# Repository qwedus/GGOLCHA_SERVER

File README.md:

# GGOOLCHA Telemetry System

DIY wireless data logging platform for Team GGOOLCHA

## Features

* 📡 Full wireless support
   * Real-time telemetry
   * Download recorded data 
   * Transmit User Events
   * Transmit CAN messages
   * Configure device (e.g. CAN bit rate)

* 📀 Up to 100 Hz data rate with various signals
   * 1x CAN 2.0(A/B)
   * 1x External GPS
   * 1x Internal 6-axis Accelerometer & Gyroscope
   * 4x Digital input channels
   * 6x Analog input channels
   * 1x Power supply voltage sensor
   * 1x Chip temperature sensor

* 💡 Customizable web-based data analysis tool
* 🍺 Fully Open-source & Open-hardware under the Beerware license

## Preview

[Web Control Hub](https://v2.monolith.luftaquila.io) for live telemetry, data viewer and device/ui configurations.

## Documentation

[Full documentation](https://v2.monolith.luftaquila.io/docs) for DIY and usage details.

## Others

The name of the project was inspired by Arthur C. Clark's novel `2001: A Space Odyssey`.

## Sponsors

The prototype PCBs for the Monolith v1, v2, and v2 mini were sponsored by [PCBWay](https://www.pcbway.com/).

For the detailed review of the manufactured PCB, see [here](https://v2.monolith.luftaquila.io/docs/#sponsor).

### Individuals

<!-- sponsors --><!-- sponsors -->

## 한계
현재는 stm32 -> esp32 -> mqtt 브로커 -> 서버 -> 프론트
stm32 -> esp32간 통신방식은 서버와 무관

JSON payload로 전달받을 경우
서버 JSON parser를 만들면 서버수정이 불필요할수도 있겠으나
 * JSON자체가 바이너리보다 무거움
 * JSON자체 오버헤드 존재등
 * WiFi자체 유선대비 지연/패킷손실 불규칙
 
 등등의 고빈도,고비용의 문제로 ESP32로는 바이너리 포맷이 적합하다고 판단.

따라서 현재로써는 Binary Payload방식을 이용할수밖에 없고 센싱을 금년과 다르게 할 경우 서버쪽 코드(protocol.js) 수정 불가피.

금년도에 사용한 ESP32의 경우 대역폭이 2.5GHZ로 낮았기때문에 호환성 최대화를 이용하여 아이폰 핫스팟이용(교내 와이파이 대역폭 5GHZ라 이용불가)

{2026년 3기 기준}

## Monolith v2 대비 변경사항
실시간 모니터링이 아닌 실시간 로깅을 목표로 했기때문에

브라우저가 MQTT브로커에 pub/sub클라이언트로 직접 접속하는 구조에 데이터 write가능한 상시 프로세스 추가구현(MQTT Logger)
시계열 DB인 influxDB 추가 구현및 운영.

다음 기수 이용을 고려하여 로컬보단 클라우드(AWS) 단일인스턴스내에 배포

deploy.yml 추가를 통해 CI/CD 구현. (GitHub 수정 즉시 서버 반영)  

센싱을 금년과 다르게 할 경우 (protocol.js)의 수정이 불가피하기에 수정의 편리함을 위해 기존에 하드 코딩되어있던 부분을 FIELD_SCHEMA 구조로 리팩토링
(필드의 추가/삭제의 경우 FIELD_SCHEMA만 변경하면 됨)

## 인프라 구축 과정

## LICENSE

For non-commercial use only:

```
"THE BEERWARE LICENSE" (Revision 42):
LUFT-AQUILA wrote this project. As long as you retain this notice,
you can do whatever you want with this stuff. If we meet someday,
and you think this stuff is worth it, you can buy me a beer in return.
```

<br>

<picture>
  <source media="(prefers-color-scheme: dark)" srcset="https://api.star-history.com/svg?repos=luftaquila/monolith&type=Date&theme=dark" />
  <source media="(prefers-color-scheme: light)" srcset="https://api.star-history.com/svg?repos=luftaquila/monolith&type=Date" />
  
</picture>

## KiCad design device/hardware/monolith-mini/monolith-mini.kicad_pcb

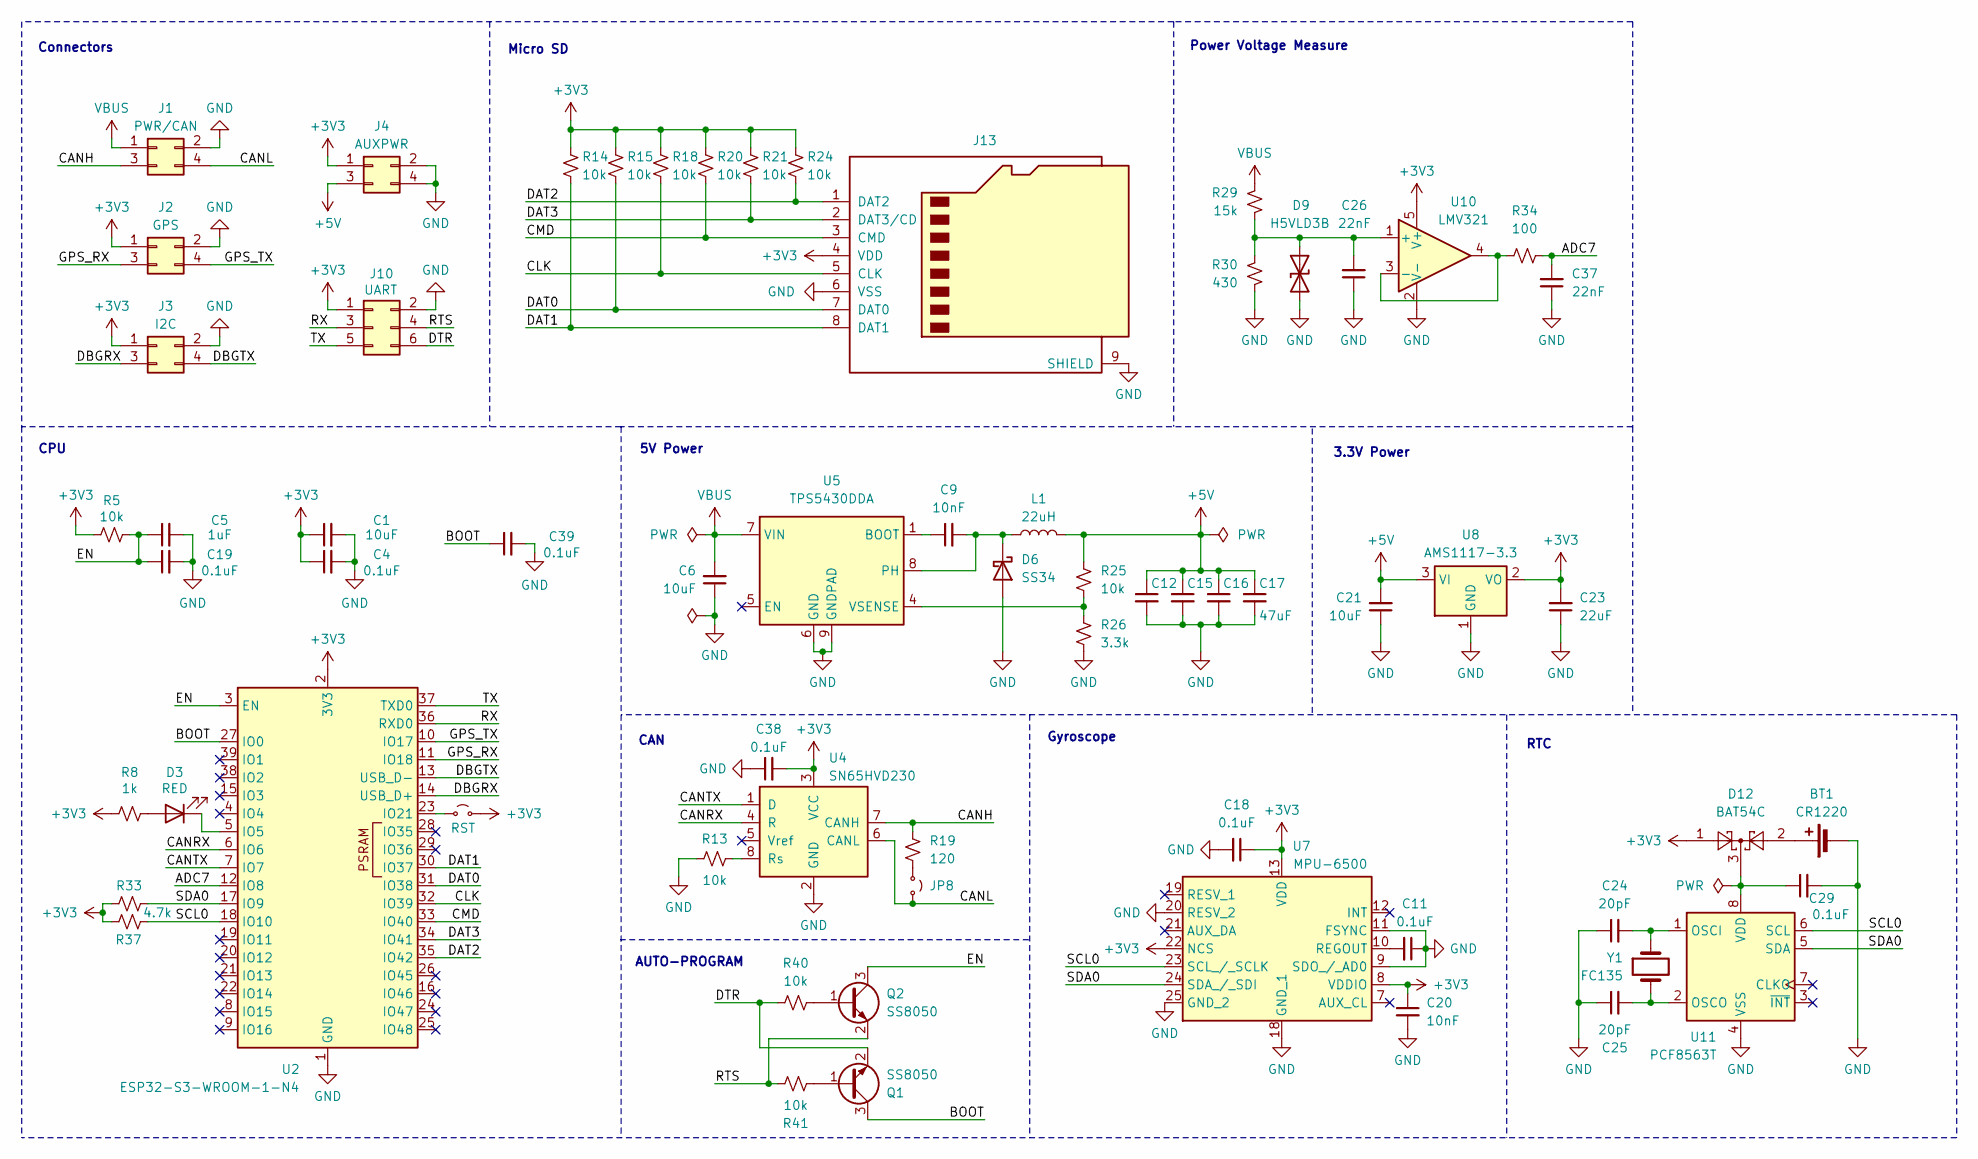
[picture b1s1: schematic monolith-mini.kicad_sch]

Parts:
BT1: CR1220; S8411-45R_1; Manufacturer_Part_Number CR1220-2; LCSC C70381
C1, C21: 10uF; C_0603_1608Metric; LCSC C19702
C4, C11, C18, C19, C29, C38, C39: 0.1uF; C_0603_1608Metric; LCSC C14663
C5: 1uF; C_0603_1608Metric; LCSC C15849
C6: 10uF; C_1206_3216Metric; LCSC C13585
C9, C20: 10nF; C_0603_1608Metric; LCSC C57112
C12, C15, C16, C17: 47uF; C_1206_3216Metric; LCSC C96123
C23: 22uF; C_0603_1608Metric; LCSC C59461
C24, C25: 20pF; C_0603_1608Metric; LCSC C1648
C26, C37: 22nF; C_0603_1608Metric; LCSC C21122
D3: RED; LED_0603_1608Metric; LCSC C2286
D6: SS34; D_SMA; LCSC C8678
D9: H5VLD3B; D_SOD-323; LCSC C20615805
D12: BAT54C; SOT-23; Manufacturer_Part_Number BAT54C; LCSC C37704
J1: PWR/CAN; Molex_Mini-Fit_Jr_5569-04A2_2x02_P4.20mm_Horizontal
J2: GPS; Molex_Mini-Fit_Jr_5569-04A2_2x02_P4.20mm_Horizontal
J3: I2C; Molex_Mini-Fit_Jr_5569-04A2_2x02_P4.20mm_Horizontal
J4: AUXPWR; Molex_Mini-Fit_Jr_5569-04A2_2x02_P4.20mm_Horizontal
J10: UART; PinHeader_2x03_P2.54mm_Vertical
J13: Micro_SD_Card; TF115BCP9; LCSC C393941
JP5: RST; PinHeader_1x02_P2.54mm_Vertical
JP8: CAN 120Ω; PinHeader_1x02_P2.54mm_Vertical
L1: 22uH; L_Sunlord_MWSA0603S; LCSC C177244
Q1, Q2: SS8050; SOT-23; LCSC C2150
R5, R13, R14, R15, R18, R20, R21, R24, R25, R40, R41: 10k; R_0603_1608Metric; LCSC C25804
R8: 1k; R_0603_1608Metric; LCSC C21190
R19: 120; R_0603_1608Metric; LCSC C22787
R26: 3.3k; R_0603_1608Metric; LCSC C22978
R29: 15k; R_0603_1608Metric; LCSC C22809
R30: 430; R_0603_1608Metric; LCSC C23170
R33, R37: 4.7k; R_0603_1608Metric; LCSC C23162
R34: 100; R_0603_1608Metric; LCSC C22775
U2: ESP32-S3-WROOM-1-N4; ESP32-S3-WROOM-1; LCSC C2913197
U4: SN65HVD230; SOIC-8_3.9x4.9mm_P1.27mm; LCSC C12084
U5: TPS5430DDA; TI_SO-PowerPAD-8_ThermalVias; LCSC C9864
U7: MPU-6500; QFN40P300X300X95-25N-D; Manufacturer_Part_Number MPU-6500; Mouser Part Number 410-MPU-6500
U8: AMS1117-3.3; SOT-223-3_TabPin2; LCSC C6186
U10: LMV321; SOT-23-5; LCSC C7972
U11: PCF8563T; SOIC-8_3.9x4.9mm_P1.27mm; LCSC C7440
Y1: FC135; Crystal_SMD_3215-2Pin_3.2x1.5mm; LCSC C32346

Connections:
+3V3: C1.1, C4.1, C18.1, C20.1, C23.2, C38.2, D12.1, J2.1, J3.1, J4.1, J10.1, J13.4 (VDD), JP5.2 (B), R5.2, R8.1, R14.2, R15.2, R18.2, R20.2, R21.2, R24.2, R33.1, R37.2, U2.2 (3V3), U4.3 (VCC), U7.8 (VDDIO), U7.13 (VDD), U7.22 (NCS), U8.2 (VO), U10.5 (V+)
+5V: C12.1, C15.1, C16.1, C17.1, C21.2, J4.3, L1.2, R25.2, U8.3 (VI)
/ADC7: C37.2, R34.2, U2.12 (IO8)
/BOOT: C39.1, Q1.3 (C), U2.27 (IO0)
/CANH: J1.3, R19.2, U4.7 (CANH)
/CANL: J1.4, JP8.2 (B), U4.6 (CANL)
/CANRX: U2.6 (IO6), U4.4 (R)
/CANTX: U2.7 (IO7), U4.1 (D)
/CLK: J13.5 (CLK), R18.1, U2.32 (IO39)
/CMD: J13.3 (CMD), R20.1, U2.33 (IO40)
/DAT0: J13.7 (DAT0), R15.1, U2.31 (IO38)
/DAT1: J13.8 (DAT1), R14.1, U2.30 (IO37)
/DAT2: J13.1 (DAT2), R24.1, U2.35 (IO42)
/DAT3: J13.2 (DAT3/CD), R21.1, U2.34 (IO41)
/DBGRX: J3.3, U2.14 (USB_D+)
/DBGTX: J3.4, U2.13 (USB_D-)
/DTR: J10.6, Q1.2 (E), R40.1
/EN: C5.1, C19.1, Q2.3 (C), R5.1, U2.3 (EN)
/GPS_RX: J2.3, U2.11 (IO18)
/GPS_TX: J2.4, U2.10 (IO17)
/RTS: J10.4, Q2.2 (E), R41.2
/RX: J10.3, U2.36 (RXD0)
/SCL0: R37.1, U2.18 (IO10), U7.23 (SCL_/_SCLK), U11.6 (SCL)
/SDA0: R33.2, U2.17 (IO9), U7.24 (SDA_/_SDI), U11.5 (SDA)
/TX: J10.5, U2.37 (TXD0)
GND: BT1.2 (-), C1.2, C4.2, C5.2, C6.1, C11.1, C12.2, C15.2, C16.2, C17.2, C18.2, C19.2, C20.2, C21.1, C23.1, C24.1, C25.1, C26.1, C29.2, C37.1, C38.1, C39.2, D6.2 (A), D9.2 (A2), J1.2, J2.2, J3.2, J4.2, J4.4, J10.2, J13.6 (VSS), J13.9 (SHIELD), R13.1, R26.1, R30.1, U2.1 (GND), U2.40 (GND), U2.41 (GND), U4.2 (GND), U5.6 (GND), U5.9 (GNDPAD), U7.9 (SDO_/_AD0), U7.11 (FSYNC), U7.18 (GND_1), U7.20 (RESV_2), U7.25 (GND_2), U8.1 (GND), U10.2 (V-), U11.4 (VSS)
unnamed: BT1.1 (+), D12.2
unnamed: D3.2 (A), R8.2
unnamed: D3.1 (K), U2.5 (IO5)
unnamed: C9.2, D6.1 (K), L1.1, U5.8 (PH)
unnamed: C26.2, D9.1 (A1), R29.1, R30.2, U10.1 (+)
unnamed: JP5.1 (A), U2.23 (IO21)
unnamed: JP8.1 (A), R19.1
unnamed: Q1.1 (B), R41.1
unnamed: Q2.1 (B), R40.2
unnamed: R13.2, U4.8 (Rs)
unnamed: C9.1, U5.1 (BOOT)
unnamed: R25.1, R26.2, U5.4 (VSENSE)
unnamed: C11.2, U7.10 (REGOUT)
unnamed: R34.1, U10.3 (-), U10.4
unnamed: C24.2, U11.1 (OSCI), Y1.1
unnamed: C25.2, U11.2 (OSCO), Y1.2
unnamed: C29.1, D12.3, U11.8 (VDD)
VBUS: C6.2, J1.1, R29.2, U5.7 (VIN)

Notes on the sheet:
CAN
AUTO-PROGRAM
Micro SD
Connectors
3.3V Power
RTC
Power Voltage Measure
CPU
Gyroscope
5V Power

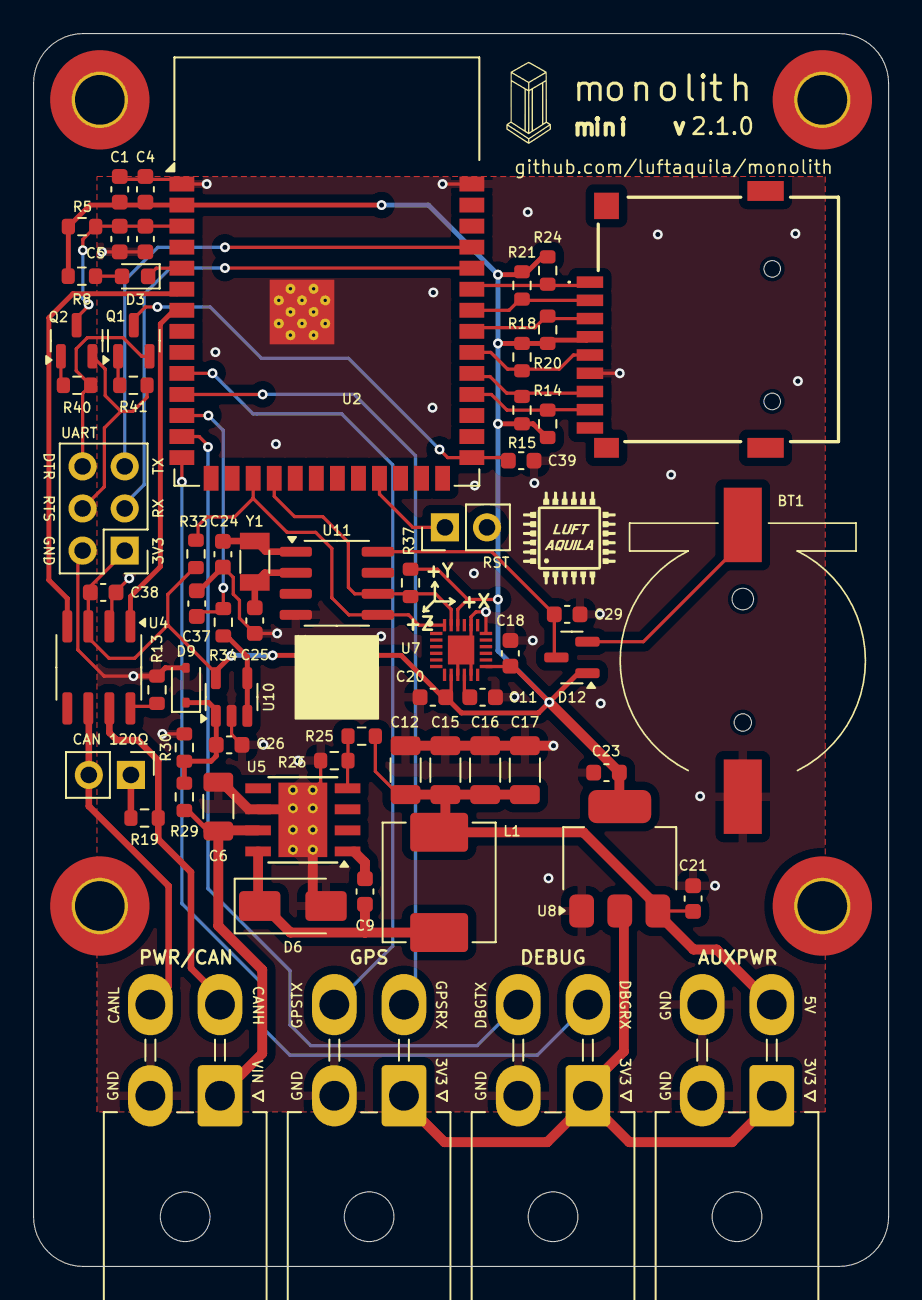
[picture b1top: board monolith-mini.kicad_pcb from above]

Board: 2 copper layers, 51.6 x 74.4 mm, 65 parts (0 on the bottom side), 44 nets.

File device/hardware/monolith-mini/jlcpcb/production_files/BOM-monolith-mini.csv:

Comment,Designator,Footprint,LCSC,Quantity
SN65HVD230,U4,SOIC-8_3.9x4.9mm_P1.27mm,C12084,1
10uF,C6,C_1206_3216Metric,C13585,1
0.1uF,"C11,C18,C19,C29,C38,C39,C4",C_0603_1608Metric,C14663,7
1uF,C5,C_0603_1608Metric,C15849,1
20pF,"C24,C25",C_0603_1608Metric,C1648,2
22uH,L1,L_Sunlord_MWSA0603S,C177244,1
10uF,"C1,C21",C_0603_1608Metric,C19702,2
H5VLD3B,D9,D_SOD-323,C20615805,1
22nF,"C26,C37",C_0603_1608Metric,C21122,2
1k,R8,R_0603_1608Metric,C21190,1
SS8050,"Q1,Q2",SOT-23,C2150,2
100,R34,R_0603_1608Metric,C22775,1
120,R19,R_0603_1608Metric,C22787,1
15k,R29,R_0603_1608Metric,C22809,1
RED,D3,LED_0603_1608Metric,C2286,1
3.3k,R26,R_0603_1608Metric,C22978,1
4.7k,"R33,R37",R_0603_1608Metric,C23162,2
430,R30,R_0603_1608Metric,C23170,1
10k,"R13,R14,R15,R18,R20,R21,R24,R25,R40,R41,R5",R_0603_1608Metric,C25804,11
ESP32-S3-WROOM-1-N4,U2,ESP32-S3-WROOM-1,C2913197,1
FC135,Y1,Crystal_SMD_3215-2Pin_3.2x1.5mm,C32346,1
BAT54C,D12,SOT-23,C37704,1
Micro_SD_Card,J13,TF115BCP9,C393941,1
MPU-6500,U7,QFN40P300X300X95-25N-D,C50278,1
10nF,"C20,C9",C_0603_1608Metric,C57112,2
22uF,C23,C_0603_1608Metric,C59461,1
AMS1117-3.3,U8,SOT-223-3_TabPin2,C6186,1
CR1220,BT1,S8411-45R_1,C70381,1
PCF8563T,U11,SOIC-8_3.9x4.9mm_P1.27mm,C7440,1
LMV321,U10,SOT-23-5,C7972,1
SS34,D6,D_SMA,C8678,1
47uF,"C12,C15,C16,C17",C_1206_3216Metric,C96123,4
TPS5430DDA,U5,TI_SO-PowerPAD-8_ThermalVias,C9864,1
